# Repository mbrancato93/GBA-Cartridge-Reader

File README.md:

# GBA-Cartridge-Reader
Cartridge ROM Reader Circuit

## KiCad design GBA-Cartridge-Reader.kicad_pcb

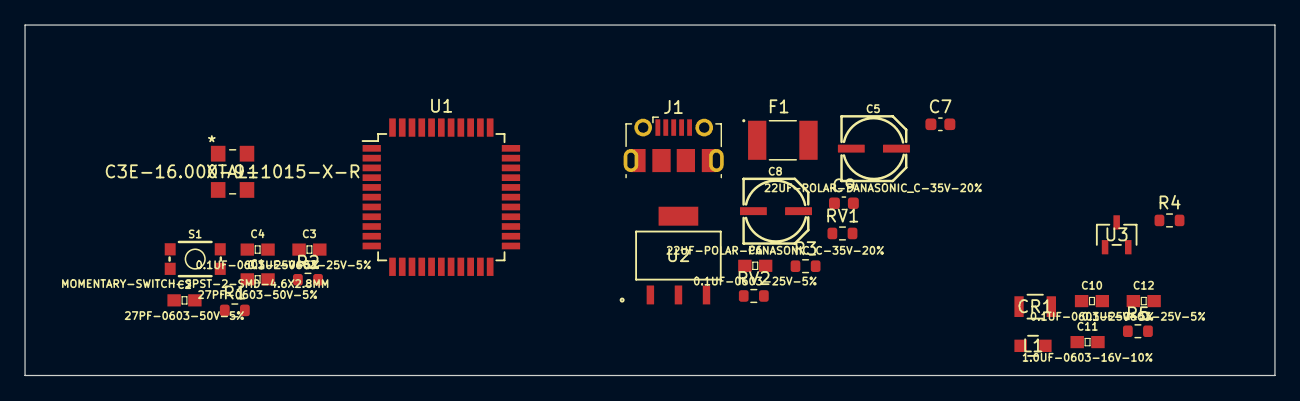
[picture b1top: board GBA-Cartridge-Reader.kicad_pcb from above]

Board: 2 copper layers, 102.4 x 28.7 mm, 28 parts (0 on the bottom side), 14 nets, no tracks yet.

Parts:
C1, C2: 27PF-0603-50V-5%; 0603
C3, C4, C6, C10, C12: 0.1UF-0603-25V-5%; 0603
C5, C8: 22UF-POLAR-PANASONIC_C-35V-20%; PANASONIC_C
C7, C9: 0.1UF-0603-25V-5%; C_0603_1608Metric
C11: 1.0UF-0603-16V-10%; 0603
CR1: CD1206-S01575; DIODE_CD1206-S01575_BRN
F1: MF-MSMF050-2; FUSM4632X85
J1: USB_B_Micro; USB_Micro-B_Molex-105017-0001
L1: MH2029-300Y; IND_BOURNS_MH2029
R1, R2: 22R; R_0603_1608Metric
R3, R4, R5: 10K; R_0603_1608Metric
RV1, RV2: Varistor_US; R_0603_1608Metric
S1: MOMENTARY-SWITCH-SPST-2-SMD-4.6X2.8MM; TACTILE_SWITCH_SMD_4.6X2.8MM
U1: ATmega32U4-A; TQFP-44_10x10mm_P0.8mm
U2: NCP1117ST50T3; SOT223-3_ONS
U3: PMV48XP_215; TO-236_SOT23_NEX
XTAL1: C3E-16.000-9-1015-X-R

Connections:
+5V: C3.2, C4.1, C8.+, C9.1, L1.1, R5.1, U1.2 (UVCC), U1.14 (VCC), U1.34 (VCC), U2.2 (OUTPUT)
D+: J1.3 (D+), R2.1, RV2.2
D-: J1.2 (D-), R1.2, RV1.2
GND: C1.1, C2.2, C3.1, C4.2, C5.-, C6.2, C7.2, C8.-, C9.2, C10.2, C11.2, C12.2, J1.5 (GND), J1.6 (Shield), R3.2, R4.2, RV1.1, RV2.1, S1.3, S1.4, U1.5 (UGND), U1.15 (GND), U1.23 (GND), U1.35 (GND), U1.43 (GND), U2.1 (ADJUST/GROUND), XTAL1.2, XTAL1.4
unnamed: C5.+, F1.1, J1.1 (VBUS)
unnamed: R1.1, U1.3 (D-)
unnamed: R2.2, U1.4 (D+)
unnamed: R5.2, S1.1, S1.2, U1.13 (~RESET)
unnamed: C11.1, U1.6 (UCAP)
unnamed: C12.1, L1.2, U1.24 (AVCC), U1.44 (AVCC)
unnamed: C10.1, U1.42 (AREF)
VSS: C7.1, F1.2, R3.1, R4.1
XTAL1: C2.1, U1.17 (XTAL1), XTAL1.3
XTAL2: C1.2, U1.16 (XTAL2), XTAL1.1

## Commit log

2023-01-21 Initial blank KiCad project.
2023-01-21 Add library for GBA components.
2023-01-22 End of Day [2023-21-01]
2023-01-22 Schematic begun with various libraries. PCB design framework established.
2023-02-06 Micro population complete.

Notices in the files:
parts and their libraries:
Copyright 2021 Accelerated Designs. All rights reserved.
